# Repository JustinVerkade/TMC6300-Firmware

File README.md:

# TMC6300-Firmware
TMC6300 developement board

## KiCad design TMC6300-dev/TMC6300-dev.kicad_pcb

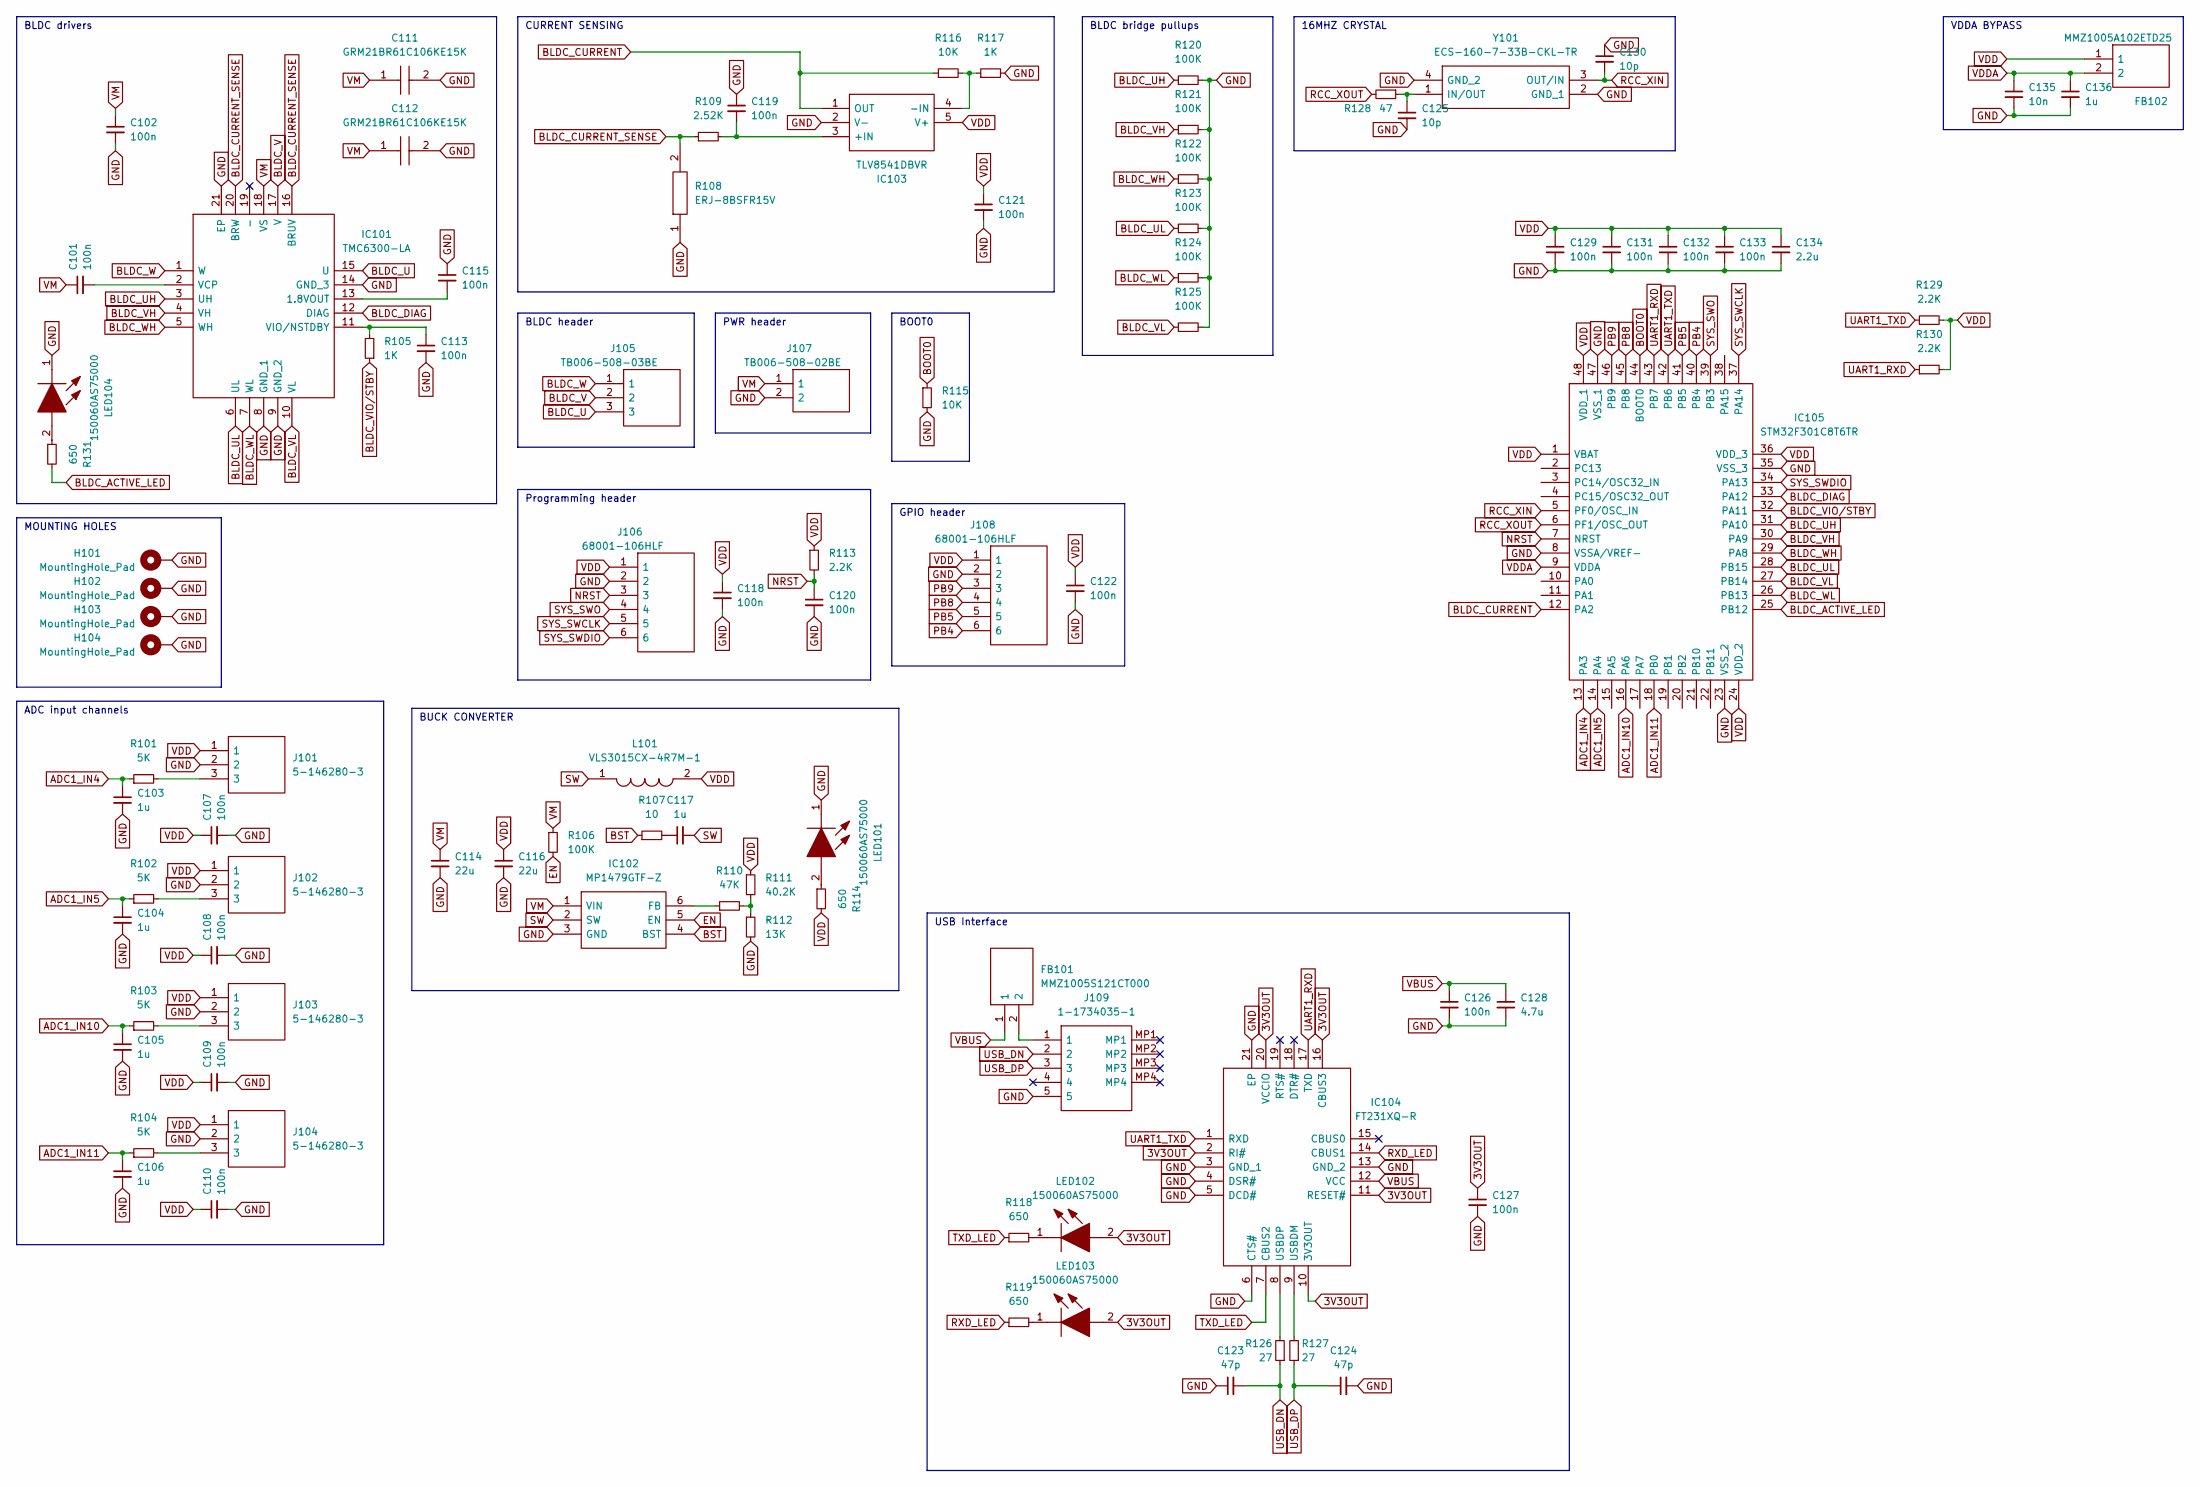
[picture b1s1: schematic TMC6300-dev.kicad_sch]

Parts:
C101, C102, C107, C108, C109, C110, C113, C115, C118, C119, C120, C121, C122, C126, C127, C129, C131, C132, C133: 100n; C_0402_1005Metric
C103, C104, C105, C106, C117, C136: 1u; C_0603_1608Metric
C111, C112: GRM21BR61C106KE15K; CAPC2012X135N; Mouser Part Number 81-GRM21BR61C106KE5K
C114, C116: 22u; C_0805_2012Metric
C123, C124: 47p; C_0402_1005Metric
C125, C130: 10p; C_0402_1005Metric
C128: 4.7u; C_0603_1608Metric
C134: 2.2u; C_0603_1608Metric
C135: 10n; C_0402_1005Metric
FB101: MMZ1005S121CT000; BEADC1005X55N; Mouser Part Number 810-MMZ1005S121CT000
FB102: MMZ1005A102ETD25; BEADC1005X55N; Mouser Part Number 810-MMZ1005A102ETD25
H101, H102, H103, H104: MountingHole_Pad; MountingHole_3.2mm_M3_Pad_Via
IC101: TMC6300-LA; QFN40P300X300X90-21N; Mouser Part Number 700-TMC6300-LA
IC102: MP1479GTF-Z; MP1479GTFZ; Mouser Part Number 946-MP1479GTF-Z
IC103: TLV8541DBVR; SOT95P280X145-5N; Mouser Part Number 595-TLV8541DBVR
IC104: FT231XQ-R; QFN50P400X400X80-21N; Mouser Part Number 895-FT231XQ-R
IC105: STM32F301C8T6TR; QFP50P900X900X160-48N; Mouser Part Number 511-STM32F301C8T6TR
J101, J102, J103, J104: 5-146280-3; HDRV3W97P0X254_1X3_721X234X821P; Mouser Part Number 571-5-146280-3
J105: TB006-508-03BE; TB00650803BE; Mouser Part Number 490-TB006-508-03BE
J106, J108: 68001-106HLF; HDRV6W67P0X254_1X6_1524X241X834P; Mouser Part Number 649-68001-106HLF
J107: TB006-508-02BE; TB00650802BE; Mouser Part Number 490-TB006-508-02BE
J109: 1-1734035-1; 117340351; Mouser Part Number 571-1-1734035-1
L101: VLS3015CX-4R7M-1; VLS3015; Manufacturer_Part_Number VLS3015CX-4R7M-1; Mouser Part Number 810-VLS3015CX-4R7M-1
LED101, LED102, LED103, LED104: 150060AS75000; LEDC1608X80N; Mouser Part Number 710-150060AS75000
R101, R102, R103, R104: 5K; R_0402_1005Metric
R105, R117: 1K; R_0402_1005Metric
R106, R120, R121, R122, R123, R124, R125: 100K; R_0402_1005Metric
R107: 10; R_0402_1005Metric
R108: ERJ-8BSFR15V; ERJ8_B_BW_R_LW_CW_D; Mouser Part Number 667-ERJ-8BSFR15V
R109: 2.52K; R_0402_1005Metric
R110: 47K; R_0402_1005Metric
R111: 40.2K; R_0402_1005Metric
R112: 13K; R_0402_1005Metric
R113, R129, R130: 2.2K; R_0402_1005Metric
R114, R118, R119, R131: 650; R_0402_1005Metric
R115, R116: 10K; R_0402_1005Metric
R126, R127: 27; R_0402_1005Metric
R128: 47; R_0402_1005Metric
Y101: ECS-160-7-33B-CKL-TR; ECS160733BCKLTR; Manufacturer_Part_Number ECS-160-7-33B-CKL-TR

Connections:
3V3OUT: C127.1, IC104.2 (RI#), IC104.10 (3V3OUT), IC104.11 (RESET#), IC104.16 (CBUS3), IC104.20 (VCCIO), LED102.2, LED103.2
ADC1_IN4: C103.1, IC105.13 (PA3), R101.1
ADC1_IN5: C104.1, IC105.14 (PA4), R102.1
ADC1_IN10: C105.1, IC105.16 (PA6), R103.1
ADC1_IN11: C106.1, IC105.18 (PB0), R104.1
BLDC_ACTIVE_LED: IC105.25 (PB12), R131.2
BLDC_CURRENT: IC103.1 (OUT), IC105.12 (PA2), R116.1
BLDC_CURRENT_SENSE: IC101.16 (BRUV), IC101.20 (BRW), R108.2, R109.1
BLDC_DIAG: IC101.12 (DIAG), IC105.33 (PA12)
BLDC_U: IC101.15 (U), J105.3
BLDC_UH: IC101.3 (UH), IC105.31 (PA10), R120.1
BLDC_UL: IC101.6 (UL), IC105.28 (PB15), R123.1
BLDC_V: IC101.17 (V), J105.2
BLDC_VH: IC101.4 (VH), IC105.30 (PA9), R121.1
BLDC_VIO/STBY: IC105.32 (PA11), R105.1
BLDC_VL: IC101.10 (VL), IC105.27 (PB14), R125.1
BLDC_W: IC101.1 (W), J105.1
BLDC_WH: IC101.5 (WH), IC105.29 (PA8), R122.1
BLDC_WL: IC101.7 (WL), IC105.26 (PB13), R124.1
BOOT0: IC105.44 (BOOT0), R115.1
BST: IC102.4 (BST), R107.1
EN: IC102.5 (EN), R106.2
GND: C102.2, C103.2, C104.2, C105.2, C106.2, C107.2, C108.2, C109.2, C110.2, C111.2, C112.2, C113.2, C114.2, C115.1, C116.2, C118.2, C119.1, C120.2, C121.2, C122.2, C123.1, C124.2, C125.2, C126.2, C127.2, C128.2, C129.2, C130.1, C131.2, C132.2, C133.2, C134.2, C135.2, C136.2, H101.1, H102.1, H103.1, H104.1, IC101.8 (GND_1), IC101.9 (GND_2), IC101.14 (GND_3), IC101.21 (EP), IC102.3 (GND), IC103.2 (V-), IC104.3 (GND_1), IC104.4 (DSR#), IC104.5 (DCD#), IC104.6 (CTS#), IC104.13 (GND_2), IC104.21 (EP), IC105.8 (VSSA/VREF-), IC105.23 (VSS_2), IC105.35 (VSS_3), IC105.47 (VSS_1), J101.2, J102.2, J103.2, J104.2, J106.2, J107.2, J108.2, J109.5, LED101.1, LED104.1, R108.1, R112.2, R115.2, R117.2, R120.2, R121.2, R122.2, R123.2, R124.2, R125.2, Y101.2 (GND_1), Y101.4 (GND_2)
NRST: C120.1, IC105.7 (NRST), J106.3, R113.2
unnamed: C101.2, IC101.2 (VCP)
unnamed: C113.1, IC101.11 (VIO/NSTDBY), R105.2
unnamed: C115.2, IC101.13 (1.8VOUT)
unnamed: C117.1, R107.2
unnamed: C119.2, IC103.3 (+IN), R109.2
unnamed: C125.1, R128.1, Y101.1 (IN/OUT)
unnamed: FB101.2, J109.1
unnamed: IC102.6 (FB), R110.1
unnamed: IC103.4 (-IN), R116.2, R117.1
unnamed: IC104.8 (USBDP), R126.2
unnamed: IC104.9 (USBDM), R127.2
unnamed: J101.3, R101.2
unnamed: J102.3, R102.2
unnamed: J103.3, R103.2
unnamed: J104.3, R104.2
unnamed: LED101.2, R114.1
unnamed: LED102.1, R118.2
unnamed: LED103.1, R119.2
unnamed: LED104.2, R131.1
unnamed: R110.2, R111.2, R112.1
PB4: IC105.40 (PB4), J108.6
PB5: IC105.41 (PB5), J108.5
PB8: IC105.45 (PB8), J108.4
PB9: IC105.46 (PB9), J108.3
RCC_XIN: C130.2, IC105.5 (PF0/OSC_IN), Y101.3 (OUT/IN)
RCC_XOUT: IC105.6 (PF1/OSC_OUT), R128.2
RXD_LED: IC104.14 (CBUS1), R119.1
SW: C117.2, IC102.2 (SW), L101.1
SYS_SWCLK: IC105.37 (PA14), J106.5
SYS_SWDIO: IC105.34 (PA13), J106.6
SYS_SWO: IC105.39 (PB3), J106.4
TXD_LED: IC104.7 (CBUS2), R118.1
UART1_RXD: IC104.17 (TXD), IC105.43 (PB7), R130.1
UART1_TXD: IC104.1 (RXD), IC105.42 (PB6), R129.1
USB_DN: C123.2, J109.2, R126.1
USB_DP: C124.1, J109.3, R127.1
VBUS: C126.1, C128.1, FB101.1, IC104.12 (VCC)
VDD: C107.1, C108.1, C109.1, C110.1, C116.1, C118.1, C121.1, C122.1, C129.1, C131.1, C132.1, C133.1, C134.1, FB102.1, IC103.5 (V+), IC105.1 (VBAT), IC105.24 (VDD_2), IC105.36 (VDD_3), IC105.48 (VDD_1), J101.1, J102.1, J103.1, J104.1, J106.1, J108.1, L101.2, R111.1, R113.1, R114.2, R129.2, R130.2
VDDA: C135.1, C136.1, FB102.2, IC105.9 (VDDA)
VM: C101.1, C102.1, C111.1, C112.1, C114.1, IC101.18 (VS), IC102.1 (VIN), J107.1, R106.1

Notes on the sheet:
BLDC header
PWR header
BLDC bridge pullups
Programming header
GPIO header
BOOT0
ADC input channels
16MHZ CRYSTAL
CURRENT SENSING
BUCK CONVERTER
BLDC drivers
VDDA BYPASS
MOUNTING HOLES
USB Interface

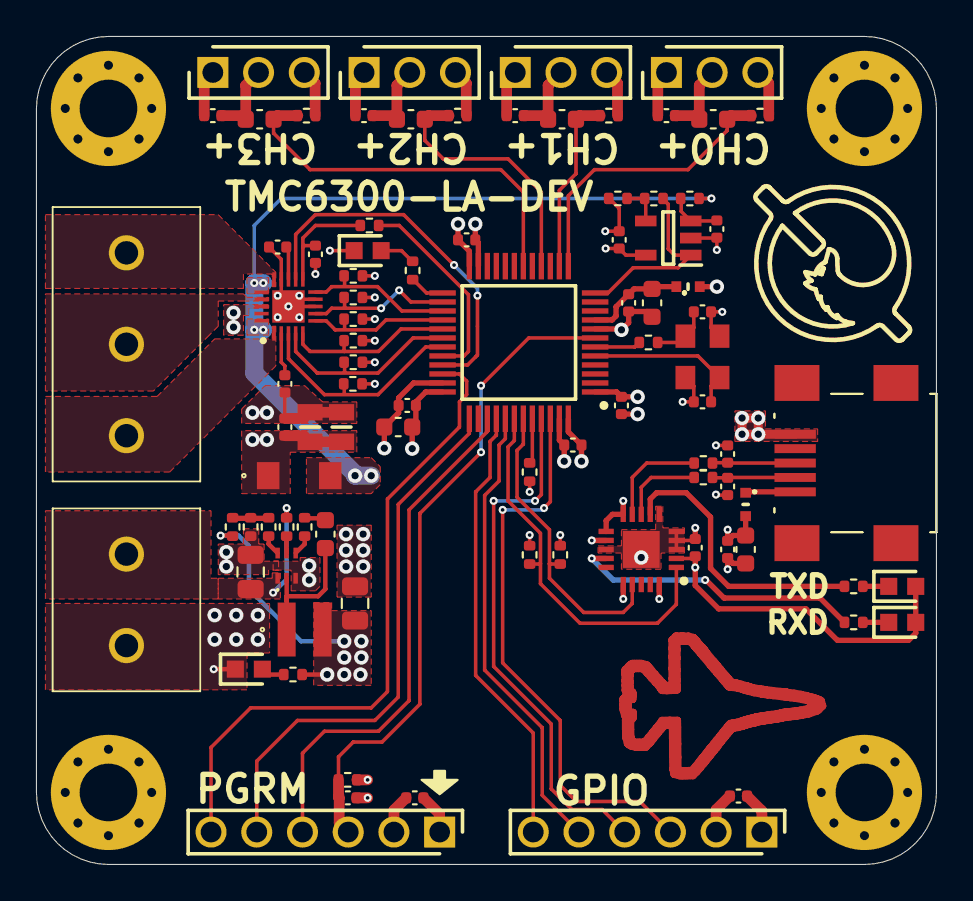
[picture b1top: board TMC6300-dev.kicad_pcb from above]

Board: 4 copper layers, 50.0 x 46.0 mm, 93 parts (0 on the bottom side), 64 nets.

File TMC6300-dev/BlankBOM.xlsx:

Id | Designator | Package |  | Designation | Supplier and ref
1 | C105,C106,C117,C104,C136,C103 | C_0603_1608Metric | 6 | 1u
2 | FB101 | BEADC1005X55N | 1 | MMZ1005S121CT000
3 | R126,R127 | R_0402_1005Metric | 2 | 27
4 | C110,C109,C120,C107,C131,C118,C127,C101,C122,C102,C126,C115,C119,C133,C121,C132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 | C_0402_1005Metric | 19 | 100n
5 | R115,R116 | R_0402_1005Metric | 2 | 10K
6 | R109 | R_0402_1005Metric | 1 | 2.52K
8 | R114,R131,R119,R118 | R_0402_1005Metric | 4 | 650
9 | R107 | R_0402_1005Metric | 1 | 10
10 | C135 | C_0402_1005Metric | 1 | 10n
11 | R117,R105 | R_0402_1005Metric | 2 | 1K
12 | R113,R129,R130 | R_0402_1005Metric | 3 | 2.2K
13 | R120,R121,R123,R106,R122,R124,R125 | R_0402_1005Metric | 7 | 100K
14 | IC104 | QFN50P400X400X80-21N | 1 | FT231XQ-R
15 | J104,J101,J103,J102 | HDRV3W97P0X254_1X3_721X234X821P | 4 | 5-146280-3
16 | Y101 | ECS160733BCKLTR | 1 | ECS-160-7-33B-CKL-TR
17 | J107 | TB00650802BE | 1 | TB006-508-02BE
18 | C111,C112 | CAPC2012X135N | 2 | GRM21BR61C106KE15K
19 | LED103,LED102,LED104,LED101 | LEDC1608X80N | 4 | 150060AS75000
20 | IC105 | QFP50P900X900X160-48N | 1 | STM32F301C8T6TR
21 | J106,J108 | HDRV6W67P0X254_1X6_1524X241X834P | 2 | 68001-106HLF
22 | R110 | R_0402_1005Metric | 1 | 47K
23 | C125,C130 | C_0402_1005Metric | 2 | 10p
24 | R108 | ERJ8_B_BW_R_LW_CW_D | 1 | ERJ-8BSFR15V
25 | J105 | TB00650803BE | 1 | TB006-508-03BE
26 | IC101 | QFN40P300X300X90-21N | 1 | TMC6300-LA
27 | C124,C123 | C_0402_1005Metric | 2 | 47p
28 | R102,R104,R103,R101 | R_0402_1005Metric | 4 | 5K
29 | IC103 | SOT95P280X145-5N | 1 | TLV8541DBVR
30 | J109 | 117340351 | 1 | 1-1734035-1
31 | R128 | R_0402_1005Metric | 1 | 47
32 | IC102 | MP1479GTFZ | 1 | MP1479GTF-Z
33 | R112 | R_0402_1005Metric | 1 | 13K
34 | C128 | C_0603_1608Metric | 1 | 4.7u
35 | FB102 | BEADC1005X55N | 1 | MMZ1005A102ETD25
36 | R111 | R_0402_1005Metric | 1 | 40.2K
37 | C134 | C_0603_1608Metric | 1 | 2.2u
38 | C114,C116 | C_0805_2012Metric | 2 | 22u
39 | L101 | VLS3015 | 1 | VLS3015CX-4R7M-1
 |  |  | 89

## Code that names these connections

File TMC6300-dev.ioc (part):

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Mcu.Name=STM32F301C(6-8)Tx
Mcu.Package=LQFP48
Mcu.UserName=STM32F301C8Tx
PA10.GPIOParameters=GPIO_Speed,GPIO_Label
PA10.GPIO_Label=BLDC_UH
PA10.GPIO_Speed=GPIO_SPEED_FREQ_MEDIUM
PA10.Signal=S_TIM1_CH3
PA11.GPIOParameters=GPIO_Speed,PinState,GPIO_Label
PA11.GPIO_Label=BLDC_VIO_STBY
PA11.GPIO_Speed=GPIO_SPEED_FREQ_LOW
PA11.PinState=GPIO_PIN_RESET
PA11.Signal=GPIO_Output
PA12.GPIOParameters=GPIO_Label
PA12.GPIO_Label=BLDC_DIAG
PA12.Signal=GPIO_Input
PA13.Mode=Trace_Asynchronous_SW
PA13.Signal=SYS_JTMS-SWDIO
PA14.Mode=Trace_Asynchronous_SW
PA14.Signal=SYS_JTCK-SWCLK
PA2.GPIOParameters=GPIO_Label
PA2.GPIO_Label=BLDC_CURRENT
PA2.Mode=IN3-Single-Ended
PA2.Signal=ADC1_IN3
PA3.Mode=IN4-Single-Ended
PA3.Signal=ADC1_IN4
PA4.Mode=IN5-Single-Ended
PA4.Signal=ADC1_IN5
PA6.Signal=ADCx_IN10
PA8.GPIOParameters=GPIO_Label
PA8.GPIO_Label=BLDC_WH
PA8.Signal=GPIO_Output
PA9.GPIOParameters=GPIO_Label
PA9.GPIO_Label=BLDC_VH
PA9.Signal=GPIO_Output
PB0.Mode=IN11-Single-Ended
PB0.Signal=ADC1_IN11
PB12.GPIOParameters=PinState,GPIO_Label
PB12.GPIO_Label=BLDC_ACTIVE_LED
PB12.PinState=GPIO_PIN_RESET
PB12.Signal=GPIO_Output
PB13.GPIOParameters=PinState,GPIO_Label
PB13.GPIO_Label=BLDC_WL
PB13.PinState=GPIO_PIN_SET
PB13.Signal=GPIO_Output
PB14.GPIOParameters=PinState,GPIO_Label
PB14.GPIO_Label=BLDC_VL
PB14.PinState=GPIO_PIN_SET
PB14.Signal=GPIO_Output
PB15.GPIOParameters=GPIO_Speed,GPIO_Label
PB15.GPIO_Label=BLDC_UL
PB15.GPIO_Speed=GPIO_SPEED_FREQ_MEDIUM
PB15.Mode=PWM Generation3 CH3 CH3N
PB15.Signal=TIM1_CH3N
PB3.Mode=Trace_Asynchronous_SW
PB3.Signal=SYS_JTDO-TRACESWO
PB4.Signal=GPIO_Output
PB5.Signal=GPIO_Output
PB8.Mode=Asynchronous
PB8.Signal=USART3_RX
PB9.Mode=Asynchronous
PB9.Signal=USART3_TX
PF0-OSC_IN.Mode=HSE-External-Oscillator
PF0-OSC_IN.Signal=RCC_OSC_IN
PF1-OSC_OUT.Mode=HSE-External-Oscillator
PF1-OSC_OUT.Signal=RCC_OSC_OUT
RCC.HSEPLLFreq_Value=8000000
RCC.HSE_VALUE=16000000
RCC.SYSCLKFreq_VALUE=72000000
RCC.SYSCLKSourceVirtual=RCC_SYSCLKSOURCE_PLLCLK
board=custom

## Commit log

2024-03-12 Added hardware files
2024-11-14 Push to Github for cleanup
